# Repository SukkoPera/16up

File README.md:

# 16UP
16UP is an Open Hardware Expansion board that will add a User Port to the Commodore 16, 116 and Plus/4 home computers.

## Summary
The biggest difference between the Commodore 16/116 and the Plus/4, besides the different amount of RAM installed, is that the former lacks a User Port. In the past there were numerous attempts at making a cartridge for the Expansion Port that would fill this gap, but apparently none of them succeeded...

... None of them except this project, of course! :) 16UP will plug into the Expansion Port and "convert" it to a User Port that will be mostly compatible with that featured on the Plus/4. It can also be used on a Plus/4 in order to gain an extra User Port.

If you are interested in this board, **please read this document carefully**, there are a few aspects that you must be aware of.

## Versions
There are currently two usable versions of 16UP:
- [Version 2](https://github.com/SukkoPera/16up/releases/tag/v2) has an onboard fully-compliant RS-232 interface. Since the Plus/4 only provides TTL-level serial signals on the User Port, it requires an external plug-in board in order to turn those into a real RS-232 port. 16UP V2 already includes the converter but this implies that the serial signals are not provided on the User Port edge connector. This is generally not a problem as most peripherals that connect to the User Port only use the parallel port it provides, but peripherals have emerged, which use both the parallel and serial signals at the same time and these cannot of course work with V2.
- [Version 3](https://github.com/SukkoPera/16up/releases/tag/v3) was developed in order to be compatible with those peripherals. The onboard RS-232 converter was removed and now the board features an 87.5% Plus/4-compatible User Port: all signals are available on the edge connector right where they should be, except /ATTN and the 9VAC power rails. These signals can still be provided through a pin header, which was extended to cover all signals in order to also facilitate scoping and experimentation. [A plug-in board was developed](https://github.com/SukkoPera/Plus4Serial) for those who need RS-232 compatibility, while [another one](https://github.com/SukkoPera/Plus4Parallel) allows for a good degree of compatiblity with DB-25 PC-style parallel ports.

Both versions are valid and fully working, it is up to the user to choose what is best for them.

## Configuration
Both versions of 16UP can be configured to respond to two different address sets through the *JP1* jumper:

### External Address
This configuration will expose the ACIA (Serial port) at address `$fd6x` and the MOS 6529 (Parallel port) at `$fd7x`. These addresses are normally unused in both the C16/116 and +4, thus this setting is the most compatible, but it will need "special" software that either looks for the ports at these addresses or that allows the addresses to be configured manually.

On a +4, this configuration will effectively add a second User Port that can be used independently of the built-in one.

### Internal Address
This configuration will expose the ACIA and MOS 6529 at the same addresses that are normally used on a +4 (`$fd0x` for the ACIA and `$fd10` for the 6529). Of course this means that it cannot be used on a +4 as the port would conflict with the built-in one. It is rather meant to be used on a C16/116, making it ALMOST (see below) compatible with all the +4 software that uses the User Port.

**NOTE: Using this board on a C16/116 requires an internal modification in the machine. While this may sound impractical, it is fairly easy to perform and there are good reasons to perform it even if you are not interested in using this board. Please [see this page](https://github.com/SukkoPera/16up/wiki/Modification) for details.**

## Caveats
If you perform the C16/116 modification, plug 16UP in the Expansion Port and want to use the Datassette, you will notice that the computer will no longer detect when you press Play upon the *Press Play on tape* prompt. This is absolutely normal and is actually a sign that the modification works as intended. If you really want to use the Datassette you can either remove the board from the Expansion Port or make a Y cable with one female and two male MiniDIN-7 connectors: the Datassette will plug into the female connector, while one of the two male ones will plug into the C16/116 and the other one into the MiniDIN-7 connector on the 16up board.

Hint: if you want to save wire and effort, it is enough to bring the *Sense* signal ([Pin 6](doc/tapeport.png)) to the connector that plugs into 16UP.

Another hint: if you use [one of these](https://github.com/SukkoPera/OpenC64TapePortBreakOut) instead of the female connector, you can make an adapter for the C64 (1530) Datassette ;).

### V2-Only
Since all the serial signals are handled on-board, they are not brought out to the edge connector. Any peripheral that uses any signals besides P1-P8, /ATTN and /RESET just won't work with V2 and that's why V3 was developed.

## Compatibility
The +4 User Port is made up of a few distinct elements, let's analyze them one by one:

### 8-bit parallel port
The 8-bit parallel port can be implemented by a few different hardware components and is fully functional. There are a few caveats though:
- On V2, bit 1 is shared with the */CTS* serial port signal: this should not cause too much concern but you should be aware that it will be forced low whenever you have something connected to the serial port that is not ready to accept data. In this case, just disconnect the device or remove the *JP2* jumper (or set it to the *HW* position). Keep in mind that **bit 1 must be high before using the serial port** (or terminals will probably never know that the other end is ready to accept data), which is the case at reset/power-on.
- Bit 2 is shared with the *Cassette Sense* signal: if you have connected the Datassette Y cable to the board, whenever a key on it is pressed, bit 2 will be forced low. If you need to use the parallel port, press Stop on the Datassette in order to release all keys.

*(Do not blame me for the above, these are questionable design decisions straight from Commodore and those problems also affect a real +4.)*

### Serial port
The +4 User Port has all the signals required by an RS-232 interface, but they are at TTL voltage levels (i.e.: 0/+5V). This is fine if you need to connect a microcontroller like an Arduino but in order to turn them into a real RS-232 port, they need to be shifted to higher voltages.

#### V3
As already mentioned, you will need to use an [extra adapter](https://github.com/SukkoPera/Plus4Serial) that plugs into the User Port edge connector. 

#### V2
16UP V2 has such an adapter built-in and thus features a full RS-232 port on the onboard DE-9 connector.

All signals on the port are connected and usable, with the exception of *Ring Indicator*. *DCD*, *DSR* and */CTS* are pulled to the asserted level in order to allow communication with devices/cables that do not use those signals.

When using the serial port, you must decide whether you want hardware flow control to be handled by the ACIA or by the KERNAL: this might sound odd but it is due to the fact that ACIA chips of the era have an hardware bug that causes the */CTS* signal to be handled incorrectly. Commodore engineers must have found that out and decided to let the KERNAL handle it (if you look at the +4 schematics, you can clearly see that the signal was rerouted at a later stage). You can make your choice through the *JP2*/*JP3* jumpers (**always move them both to the same side!**): the *SW* setting will pass */CTS* to the KERNAL and is the recommended one as this is the configuration used on the +4. The *HW* position is only recommended if you are using a W65C51S chip (which should have fixed the bug) and is mainly meant as an experimental feature.

If you are looking for a terminal emulator, I recommend [Term-80](https://plus4world.powweb.com/software/Term-80_English) as it is hands down the most feature-rich program of its kind (Hint: press <kbd>CBM+HELP</kbd> when you get lost) and supports communication at 19200 bps (Take that, C64!).

### /RESET signal
This is fully functional as on the original +4.

### /ATTENTION signal
The /ATTENTION signal is not present on the C16/116 Expansion Port. Thus, if you need it, you will need to provide the board with it through the */ATTN* (*J1*) connector on V2 or through the relevant pin of the *J3* pin header on V3. The signal is available on pin 3 of the [IEC (Serial) port](doc/iec_serial.png) and it can be connected in parallel to any other device you already have on that port, just break it out.

### +5VDC power supply
This is directly connected to the main power rails of the C16/116. Use common sense and do not draw "too much" power out of it.

### 9VAC power supply
This is not present on the C16/116 Expansion Port and thus the corresponding pins of the User Port are left unconnected on V2, while on V3 they can be powered from the relevant pins of the *J3* pin header. This should not be a big deal though, as the main use case for this is to provide the higher voltages needed for a fully-compliant RS-232 interface but 16UP V2 has that built-in in a way that does not require an actual higher-voltage supply, and the same applies for the recommended adapter for V3. Let me know if you find any User Port peripherals that require it.

## Assembly
The parallel port on the +4 is driven through a MOS 6529 (U2 on the board). Since these days that IC is pretty hard to get hold of, an alternative circuit based on a 74LS654 was designed by Daniël Mantione and integrated into the board. Depending on what you choose to use:
- If you use an original MOS 6529: do NOT mount RN1.
- If you use a 74LS654: mount RN1.

There are various ICs that can be used as ACIA (U3):
- Original MOS 6551 or 8551 will work but are hard to find.
- The Western Design Center still produces the [W65C51S](https://www.westerndesigncenter.com/wdc/w65c51s-chip.php), which is based on the original MOS design and is fully compatible with it. There is also an -N model but its compatibility is uncertain at this stage.
- Older similar chips recovered from older equipment, such as the Rockwell R6551(A)P, UMC UM6551(A), etc. can be found on Aliexpress, eBay, etc. easily and cheaply and should be perfectly compatible. Prefer models with an *A* in the part number. I did all my testing with an R6551P, by the way.

The board uses a GAL for address decoding. Either a GAL20 or GAL22 can be used and both can be programmed with the ubiquitous TL866 programmers. The required JED files can be found in the relevant directories. The GAL speed shouldn't matter too much, I used a 25ns model with no particular issues.

## License
The 16UP documentation, including the design itself, is copyright &copy; SukkoPera 2022-2023 and is licensed under the [Creative Commons Attribution-NonCommercial-ShareAlike 4.0 International License](https://creativecommons.org/licenses/by-nc-sa/4.0/).

This documentation is distributed *as is* and WITHOUT ANY EXPRESS OR IMPLIED WARRANTIES whatsoever with respect to its functionality, operability or use, including, without limitation, any implied warranties OF MERCHANTABILITY, SATISFACTORY QUALITY, FITNESS FOR A PARTICULAR PURPOSE or infringement. We expressly disclaim any liability whatsoever for any direct, indirect, consequential, incidental or special damages, including, without limitation, lost revenues, lost profits, losses resulting from business interruption or loss of data, regardless of the form of action or legal theory under which the liability may be asserted, even if advised of the possibility or likelihood of such damages.

## Support the Project
If you want to get some boards manufactured, you can get them from PCBWay through this link:

### V2

### V3

You get my gratitude and cheap, professionally-made and good quality PCBs, I get some credit that will help with this and [other projects](https://www.pcbway.com/project/member/shareproject/?bmbid=41100). You won't even have to worry about the various PCB options, it's all pre-configured for you!

Also, if you still have to register, [you can use this link](https://www.pcbway.com/setinvite.aspx?inviteid=41100) to get some bonus initial credit (and yield me some more).

You can also buy me a coffee if you want:

## Thanks
Inspiration for this board came from an uncompleted [project by Solder/Synergy](http://solder-synergy.de/plus4/hardware/index.html).

Other people from the [Plus/4 World Forum](https://plus4world.powweb.com/forum) helped, in particular:
* Daniël Mantione for the [MOS 6529 replacement circuit](https://www.sellmyretro.com/offer/details/mos-6529-spi-full-equivalent--_-soldering-kit-43923).
* TLC (Levente Hársfalvi) for lots of information about the serial port.
* MCes for helping fine-tuning of the C16 modification.

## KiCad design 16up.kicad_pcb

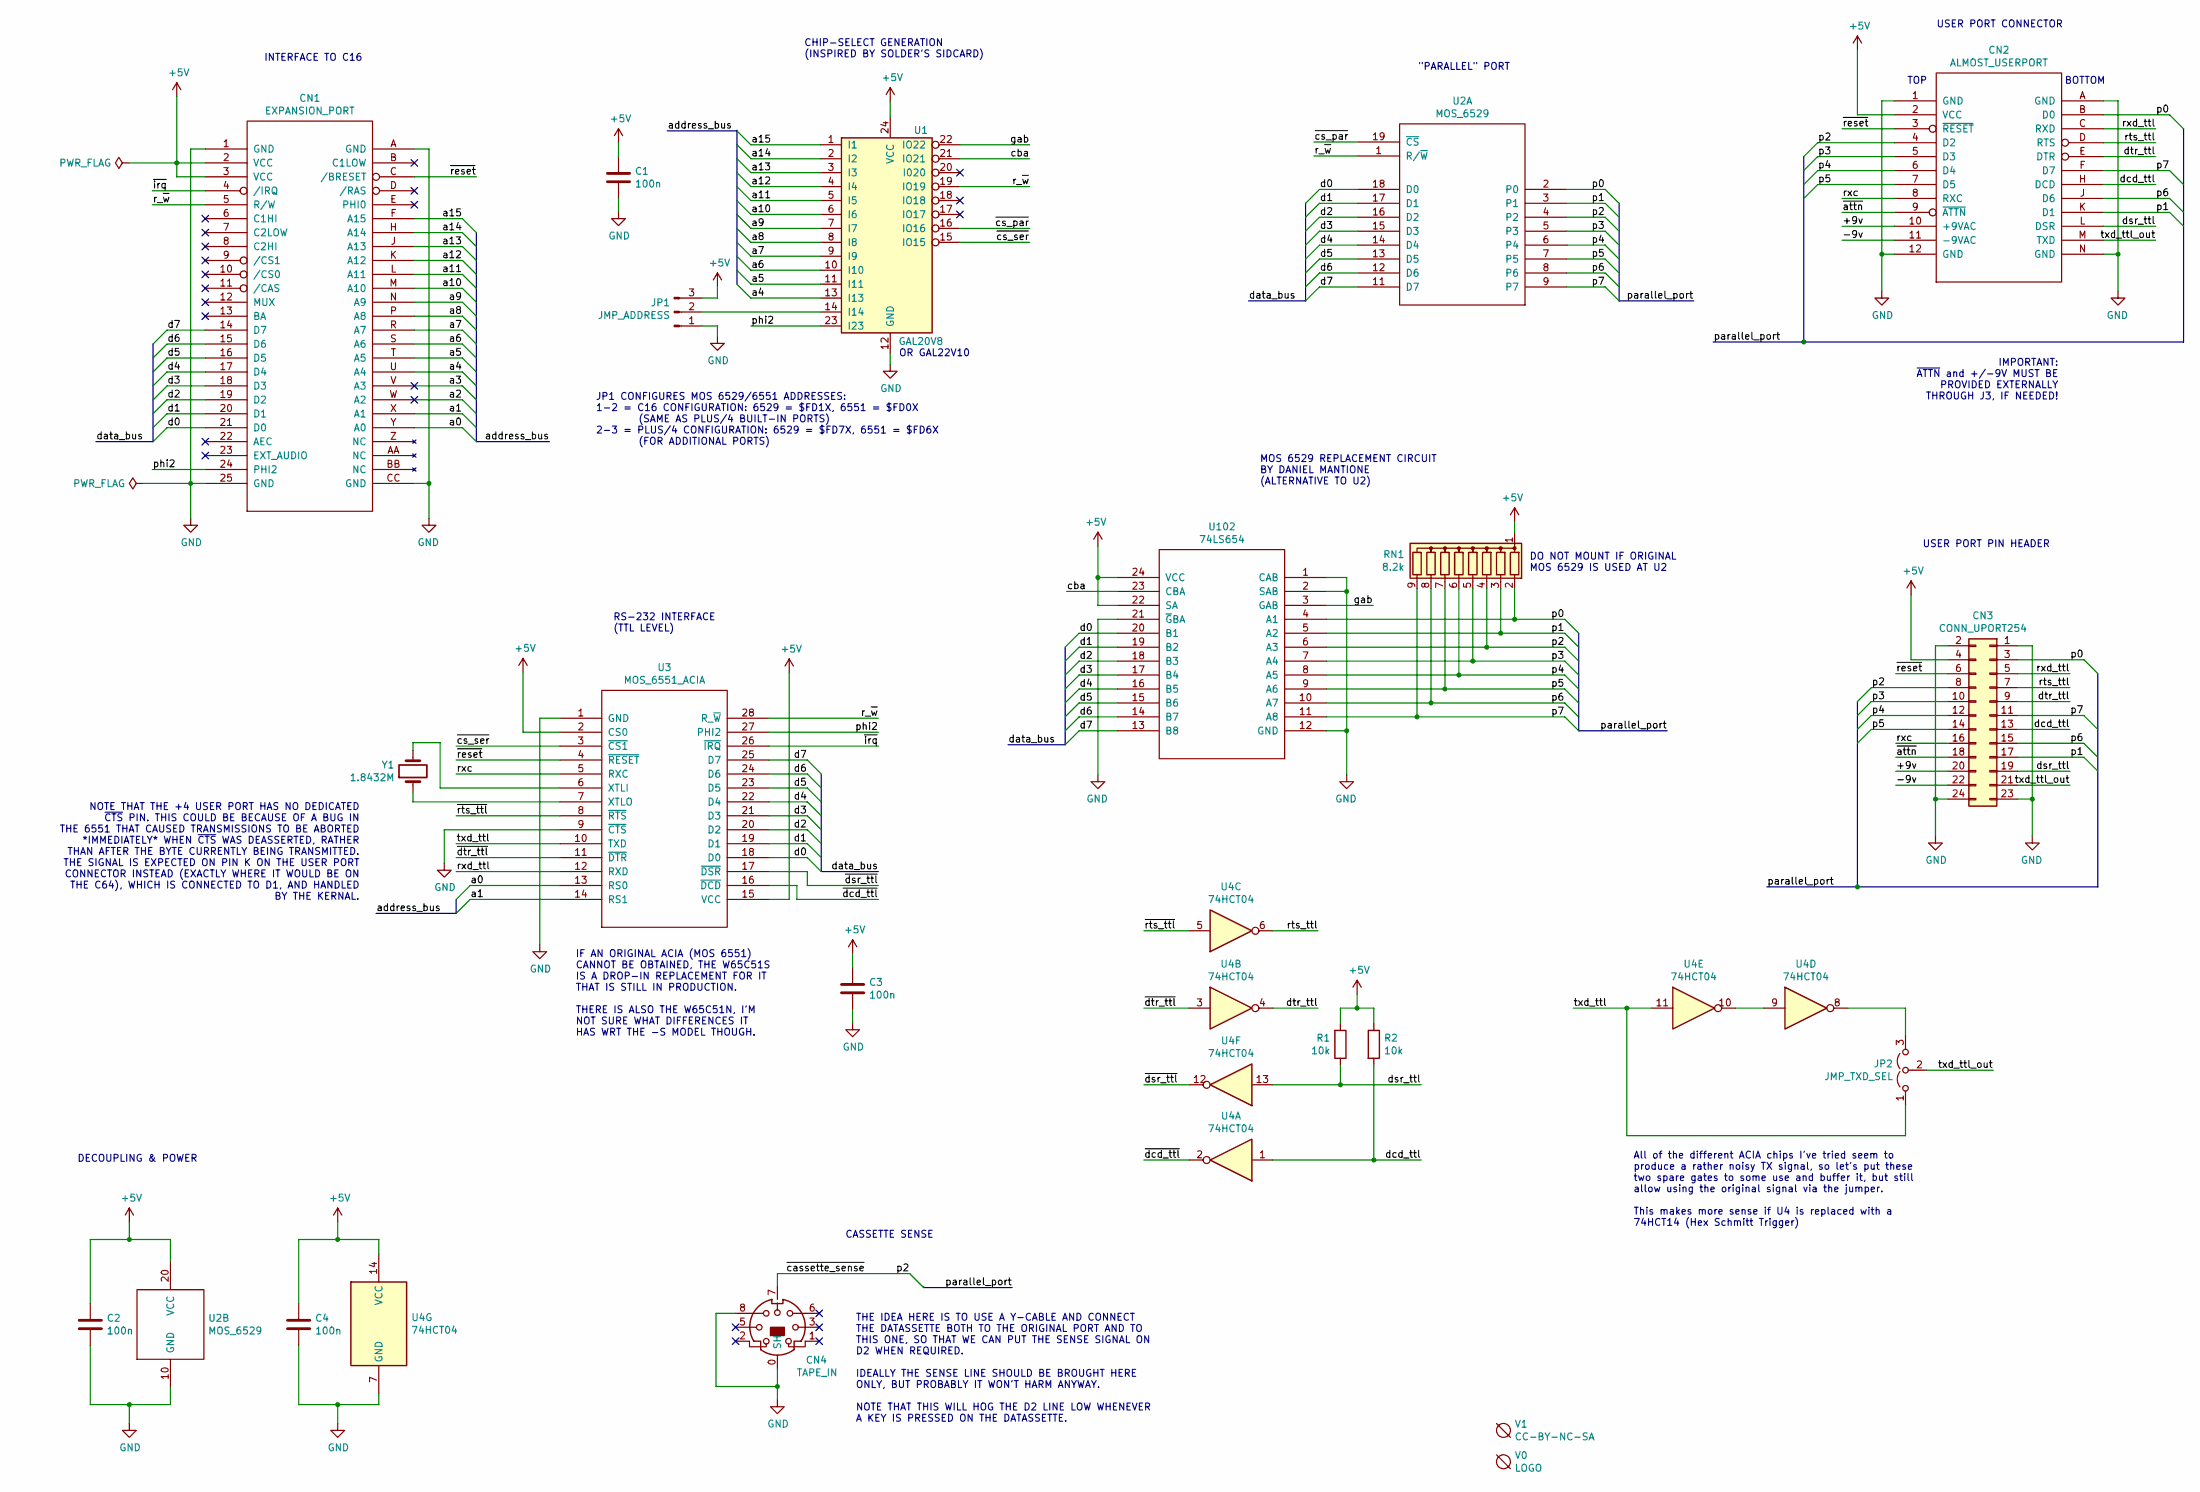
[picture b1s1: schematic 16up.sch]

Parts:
C1, C2, C3, C4: 100n; C_Disc_D7.0mm_W2.5mm_P5.00mm; MouserPN 810-FG28X7R1H104KNT0
CN1: EXPANSION_PORT; C16_Cart_Conn; MouserPN ---
CN2: ALMOST_USERPORT; Plus4_UserPort; MouserPN ---
CN3: CONN_UPORT254; PinHeader_2x12_P2.54mm_Vertical
CN4: TAPE_IN; KMDGX-7S-BS
JP1: JMP_ADDRESS; PinHeader_1x03_P2.54mm_Vertical
JP2: JMP_TXD_SEL; SolderJumper-3_P1.3mm_Open_RoundedPad1.0x1.5mm
R1, R2: 10k; R_Axial_DIN0207_L6.3mm_D2.5mm_P2.54mm_Vertical
RN1: 8.2k; R_Array_SIP9
U1: GAL20V8; DIP-24_W7.62mm_Socket_LongPads; MouserPN 556-AF22V10C15PU
U2: MOS_6529; DIP-20_W7.62mm_Socket_LongPads
U3: MOS_6551_ACIA; DIP-28_W15.24mm_Socket_LongPads
U4: 74HCT04; DIP-14_W7.62mm_Socket_LongPads
U102: 74LS654; DIP-24_W7.62mm_Socket_LongPads
V0: LOGO; logo; MouserPN ---
V1: CC-BY-NC-SA; cc_by_nc_sa; MouserPN ---
Y1: 1.8432M; Crystal_HC49-U_Vertical; MouserPN 520-HCA184-SX

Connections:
+5V: C1.1, C2.1, C3.1, C4.1, CN1.2 (VCC), CN1.3 (VCC), CN2.2 (VCC), CN3.4, JP1.3, R1.2, R2.1, RN1.1 (common), U1.24 (VCC), U2.20 (VCC), U3.2 (CS0), U3.15 (VCC), U4.14 (VCC), U102.22 (SA), U102.24 (VCC)
/+9v: CN2.10 (+9VAC), CN3.20
/-9v: CN2.11 (-9VAC), CN3.22
/a0: CN1.Y (A0), U3.13 (RS0)
/a1: CN1.X (A1), U3.14 (RS1)
/a2: CN1.W (A2)
/a3: CN1.V (A3)
/a4: CN1.U (A4), U1.13 (I13)
/a5: CN1.T (A5), U1.11 (I11)
/a6: CN1.S (A6), U1.10 (I10)
/a7: CN1.R (A7), U1.9 (I9)
/a8: CN1.P (A8), U1.8 (I8)
/a9: CN1.N (A9), U1.7 (I7)
/a10: CN1.M (A10), U1.6 (I6)
/a11: CN1.L (A11), U1.5 (I5)
/a12: CN1.K (A12), U1.4 (I4)
/a13: CN1.J (A13), U1.3 (I3)
/a14: CN1.H (A14), U1.2 (I2)
/a15: CN1.F (A15), U1.1 (I1)
/cba: U1.21 (IO21), U102.23 (CBA)
/d0: CN1.21 (D0), U2.18 (D0), U3.18 (D0), U102.20 (B1)
/d1: CN1.20 (D1), U2.17 (D1), U3.19 (D1), U102.19 (B2)
/d2: CN1.19 (D2), U2.16 (D2), U3.20 (D2), U102.18 (B3)
/d3: CN1.18 (D3), U2.15 (D3), U3.21 (D3), U102.17 (B4)
/d4: CN1.17 (D4), U2.14 (D4), U3.22 (D4), U102.16 (B5)
/d5: CN1.16 (D5), U2.13 (D5), U3.23 (D5), U102.15 (B6)
/d6: CN1.15 (D6), U2.12 (D6), U3.24 (D6), U102.14 (B7)
/d7: CN1.14 (D7), U2.11 (D7), U3.25 (D7), U102.13 (B8)
/dcd_ttl: CN2.H (DCD), CN3.13, R2.2, U4.1
/dsr_ttl: CN2.L (DSR), CN3.19, R1.1, U4.13
/dtr_ttl: CN2.E (DTR), CN3.9, U4.4
/gab: U1.22 (IO22), U102.3 (GAB)
/p0: CN2.B (D0), CN3.3, RN1.2 (R1), U2.2 (P0), U102.4 (A1)
/p1: CN2.K (D1), CN3.17, RN1.3 (R2), U2.3 (P1), U102.5 (A2)
/p2: CN2.4 (D2), CN3.8, CN4.7, RN1.4 (R3), U2.4 (P2), U102.6 (A3)
/p3: CN2.5 (D3), CN3.10, RN1.5 (R4), U2.5 (P3), U102.7 (A4)
/p4: CN2.6 (D4), CN3.12, RN1.6 (R5), U2.6 (P4), U102.8 (A5)
/p5: CN2.7 (D5), CN3.14, RN1.7 (R6), U2.7 (P5), U102.9 (A6)
/p6: CN2.J (D6), CN3.15, RN1.8 (R7), U2.8 (P6), U102.10 (A7)
/p7: CN2.F (D7), CN3.11, RN1.9 (R8), U2.9 (P7), U102.11 (A8)
/phi2: CN1.24 (PHI2), U1.23 (I23), U3.27 (PHI2)
/r_~w: CN1.5 (R/W), U1.19 (IO19), U2.1 (R/~W), U3.28 (R_~W)
/rts_ttl: CN2.D (RTS), CN3.7, U4.6
/rxc: CN2.8 (RXC), CN3.16, U3.5 (RXC)
/rxd_ttl: CN2.C (RXD), CN3.5, U3.12 (RXD)
/txd_ttl: JP2.1 (A), U3.10 (TXD), U4.11
/txd_ttl_out: CN2.M (TXD), CN3.21, JP2.2 (C)
/~attn: CN2.9 (~ATTN), CN3.18
/~cs_par: U1.16 (IO16), U2.19 (~CS)
/~cs_ser: U1.15 (IO15), U3.3 (~CS1)
/~dcd_ttl: U3.16 (~DCD), U4.2
/~dsr_ttl: U3.17 (~DSR), U4.12
/~dtr_ttl: U3.11 (~DTR), U4.3
/~irq: CN1.4 (/IRQ), U3.26 (~IRQ)
/~reset: CN1.C (/BRESET), CN2.3 (~RESET), CN3.6, U3.4 (~RESET)
/~rts_ttl: U3.8 (~RTS), U4.5
GND: C1.2, C2.2, C3.2, C4.2, CN1.1 (GND), CN1.25 (GND), CN1.A (GND), CN1.CC (GND), CN2.1 (GND), CN2.12 (GND), CN2.A (GND), CN2.N (GND), CN3.1, CN3.2, CN3.23, CN3.24, CN4.0 (SH), CN4.8, JP1.1, U1.12 (GND), U2.10 (GND), U3.1 (GND), U3.9 (~CTS), U4.7 (GND), U102.1 (CAB), U102.2 (SAB), U102.12 (GND), U102.21 (~G~BA)
unnamed: JP1.2, U1.14 (I14)
unnamed: JP2.3 (B), U4.8
unnamed: U3.6 (XTLI), Y1.2
unnamed: U3.7 (XTLO), Y1.1
unnamed: U4.9, U4.10

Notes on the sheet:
CHIP-SELECT GENERATION (INSPIRED BY SOLDER'S SIDCARD)
IMPORTANT: ~ATTN~ and +/-9V MUST BE PROVIDED EXTERNALLY THROUGH J3, IF NEEDED!
"PARALLEL" PORT
USER PORT CONNECTOR
INTERFACE TO C16
NOTE THAT THE +4 USER PORT HAS NO DEDICATED ~CTS~ PIN. THIS COULD BE BECAUSE OF A BUG IN THE 6551 THAT CAUSED TRANSMISSIONS TO BE ABORTED *IMMEDIATELY* WHEN ~CTS~ WAS DEASSERTED, RATHER THAN AFTER THE BYTE CURRENTLY BEING TRANSMITTED. THE SIGNAL IS EXPECTED ON PIN K ON THE USER PORT CONNECTOR INSTE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
IF AN ORIGINAL ACIA (MOS 6551) CANNOT BE OBTAINED, THE W65C51S IS A DROP-IN REPLACEMENT FOR IT THAT IS STILL IN PRODUCTION. THERE IS ALSO THE W65C51N, I'M NOT SURE WHAT DIFFERENCES IT HAS WRT THE -S MODEL THOUGH.
RS-232 INTERFACE (TTL LEVEL)
DECOUPLING & POWER
TOP
BOTTOM
JP1 CONFIGURES MOS 6529/6551 ADDRESSES: 1-2 = C16 CONFIGURATION: 6529 = $FD1X, 6551 = $FD0X (SAME AS PLUS/4 BUILT-IN PORTS) 2-3 = PLUS/4 CONFIGURATION: 6529 = $FD7X, 6551 = $FD6X (FOR ADDITIONAL PORTS)
OR GAL22V10
CASSETTE SENSE
THE IDEA HERE IS TO USE A Y-CABLE AND CONNECT THE DATASSETTE BOTH TO THE ORIGINAL PORT AND TO THIS ONE, SO THAT WE CAN PUT THE SENSE SIGNAL ON D2 WHEN REQUIRED. IDEALLY THE SENSE LINE SHOULD BE BROUGHT HERE ONLY, BUT PROBABLY IT WON'T HARM ANYWAY. NOTE THAT THIS WILL HOG THE D2 LINE LOW WHENEVER A 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
USER PORT PIN HEADER
DO NOT MOUNT IF ORIGINAL MOS 6529 IS USED AT U2
MOS 6529 REPLACEMENT CIRCUIT BY DANIEL MANTIONE (ALTERNATIVE TO U2)
All of the different ACIA chips I've tried seem to produce a rather noisy TX signal, so let's put these two spare gates to some use and buffer it, but still allow using the original signal via the jumper. This makes more sense if U4 is replaced with a 74HCT14 (Hex Schmitt Trigger)

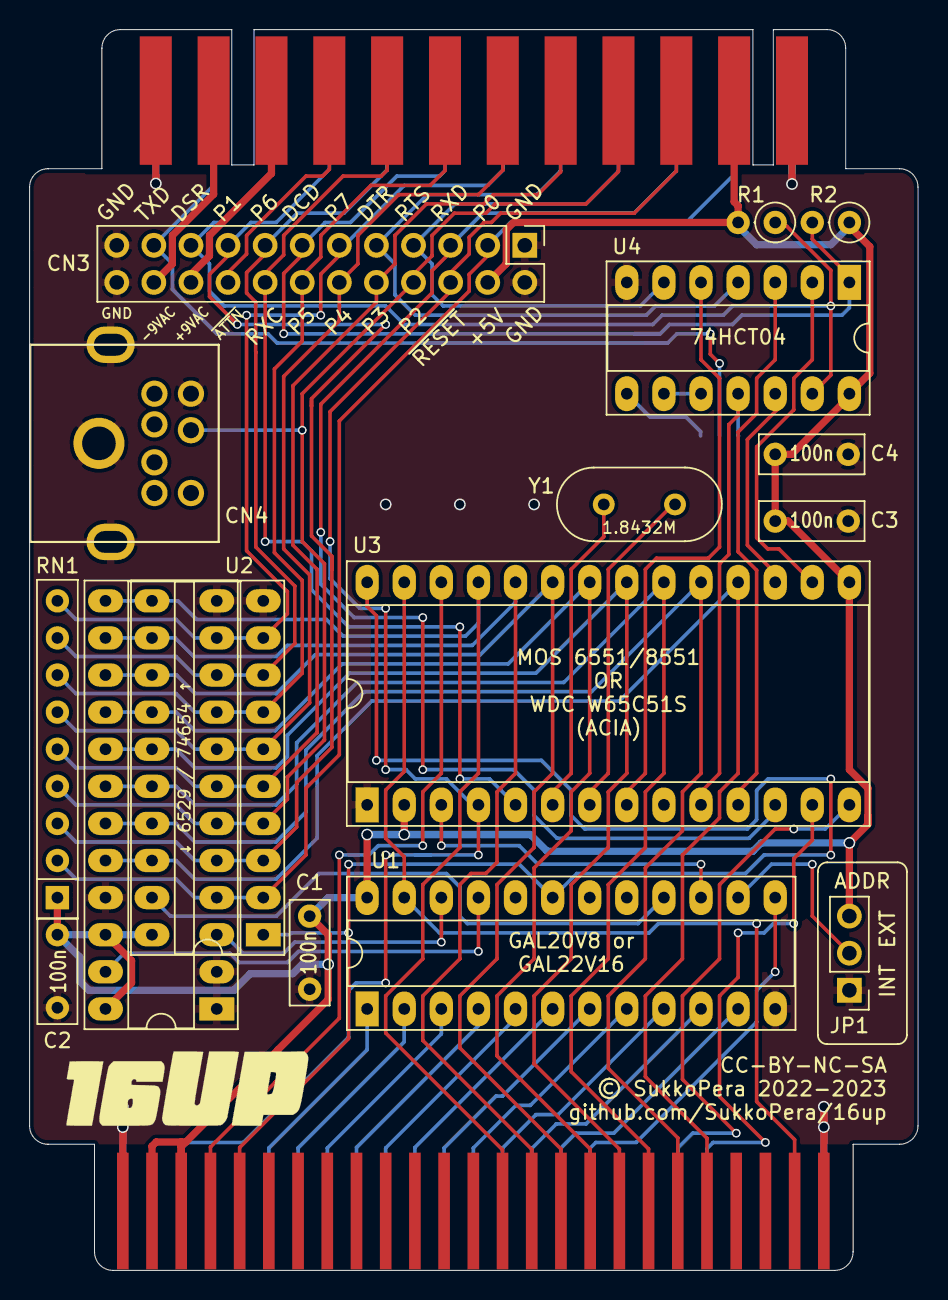
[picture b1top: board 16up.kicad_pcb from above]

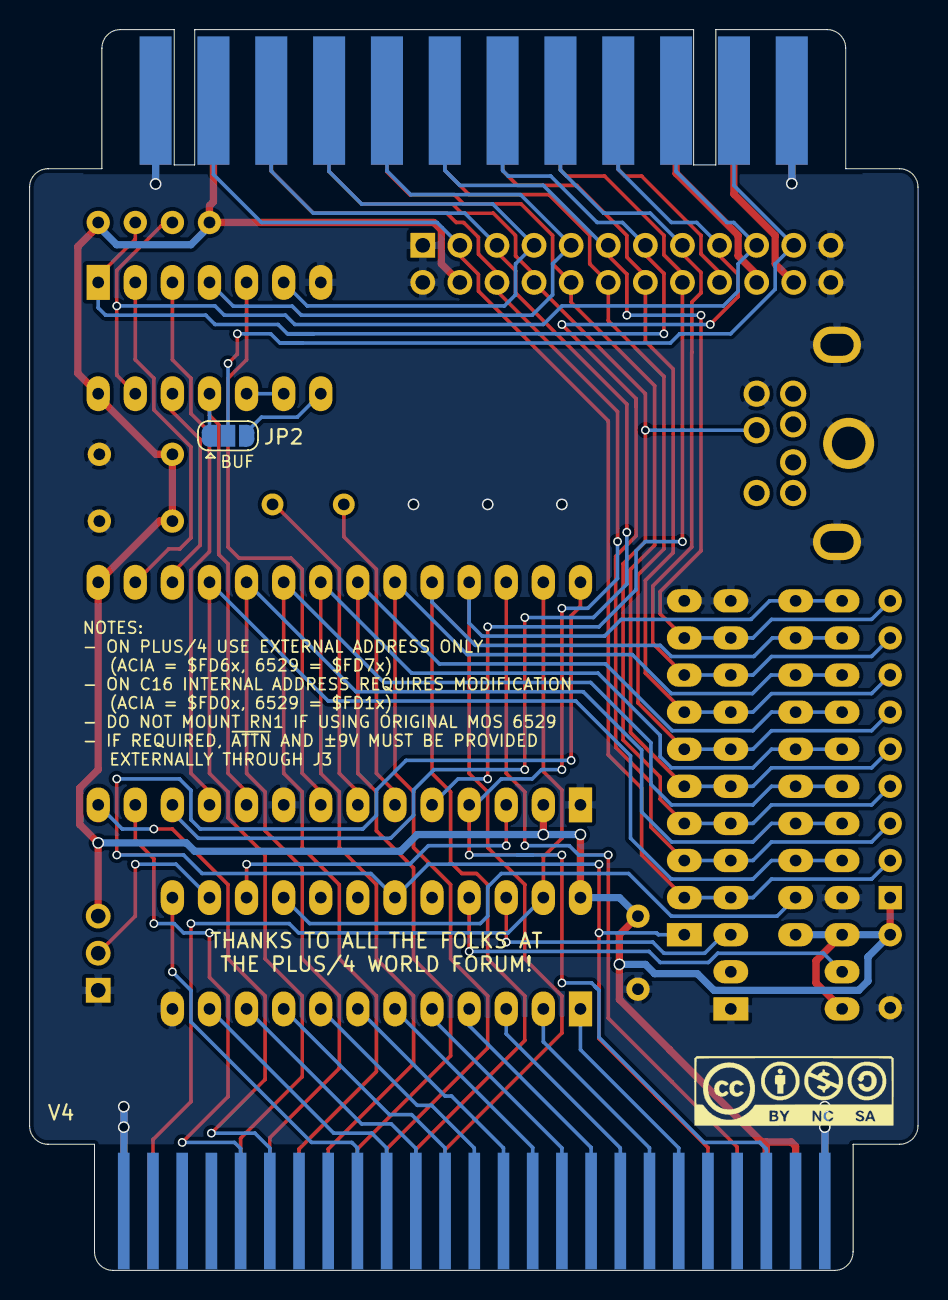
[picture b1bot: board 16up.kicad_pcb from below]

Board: 2 copper layers, 60.8 x 85.0 mm, 21 parts (2 on the bottom side), 60 nets.

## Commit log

2022-09-02 Assign footprints
2022-09-04 Fix some warnings
2022-09-04 (Very) Rough routing done
2022-09-06 Improve routing
2022-09-06 Almost there
2022-09-07 Swap top/bottom pins of edge connector Sigh...
2022-09-13 Move /CTS to PC2
2022-09-17 Almost ready for prototypes
2022-09-17 Final touches
2022-09-17 ExtraUserPort -> 16up
2022-09-18 Fix userport connector !!!
2022-09-18 Add README
2022-09-18 Add schematics PDF
2022-09-21 Remove serial signals from Userport connector They wouldn't work anyway, as whatever gets connected there expects all control signals to be inverted as per Commodore serial port standards.
2022-09-28 Pull-up signals at the RS-232 port
2022-10-17 Add GAL20/22 equations
2022-10-17 Get rid of protruding track
2022-10-17 Add C2 value on silkscreen
2022-10-22 Fix /CTS
2022-10-22 Generate active-high CTS through the GAL
2022-10-22 Use better MiniDIN-7 footprint The former was actually a MiniDIN-8...
2022-10-23 Fix track alignment
2022-10-23 Add renders
2022-10-23 Add C116 mentions
2022-11-02 Unify GAL20/22 equations
2022-12-02 Move crystal above U3 for easier insertion These crystals are always too tall...
2022-12-02 Improve ground plane
2022-12-02 Add test images
2022-12-07 Only support 74x654 as 6529 replacement
2022-12-07 Update renders
2023-03-07 Start 232-less version
2023-03-13 Routing done
2023-03-13 Ground unused gates of U4
2023-03-15 Do not let soldermask between fingers of top connector
2023-08-13 Update README for V3
2023-08-13 Update renders and board link
2024-03-24 Close #3
2024-09-08 Add optional buffering for TX

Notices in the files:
16up.kicad_pcb:
Licensed under CC BY-NC-SA 4.0
